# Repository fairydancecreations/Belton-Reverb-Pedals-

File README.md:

# Belton-Reverb-Pedals-
2 schims and pcb +gerbers for a BH2 and a BH3 belton brick reverbs. note the tone stack before the gain. seems stupid right ? have faith and try it with modulations. the BJT boost after is to give it level. both pcbs and circuits have parts to be included and changed to make overdrive versions. simply add the 2 soft clipping diodes . pick your fave and change the gain pot from 100k to 500k . this is a loud pedal so take the vol pot down to 50k if your speakers are in danger.

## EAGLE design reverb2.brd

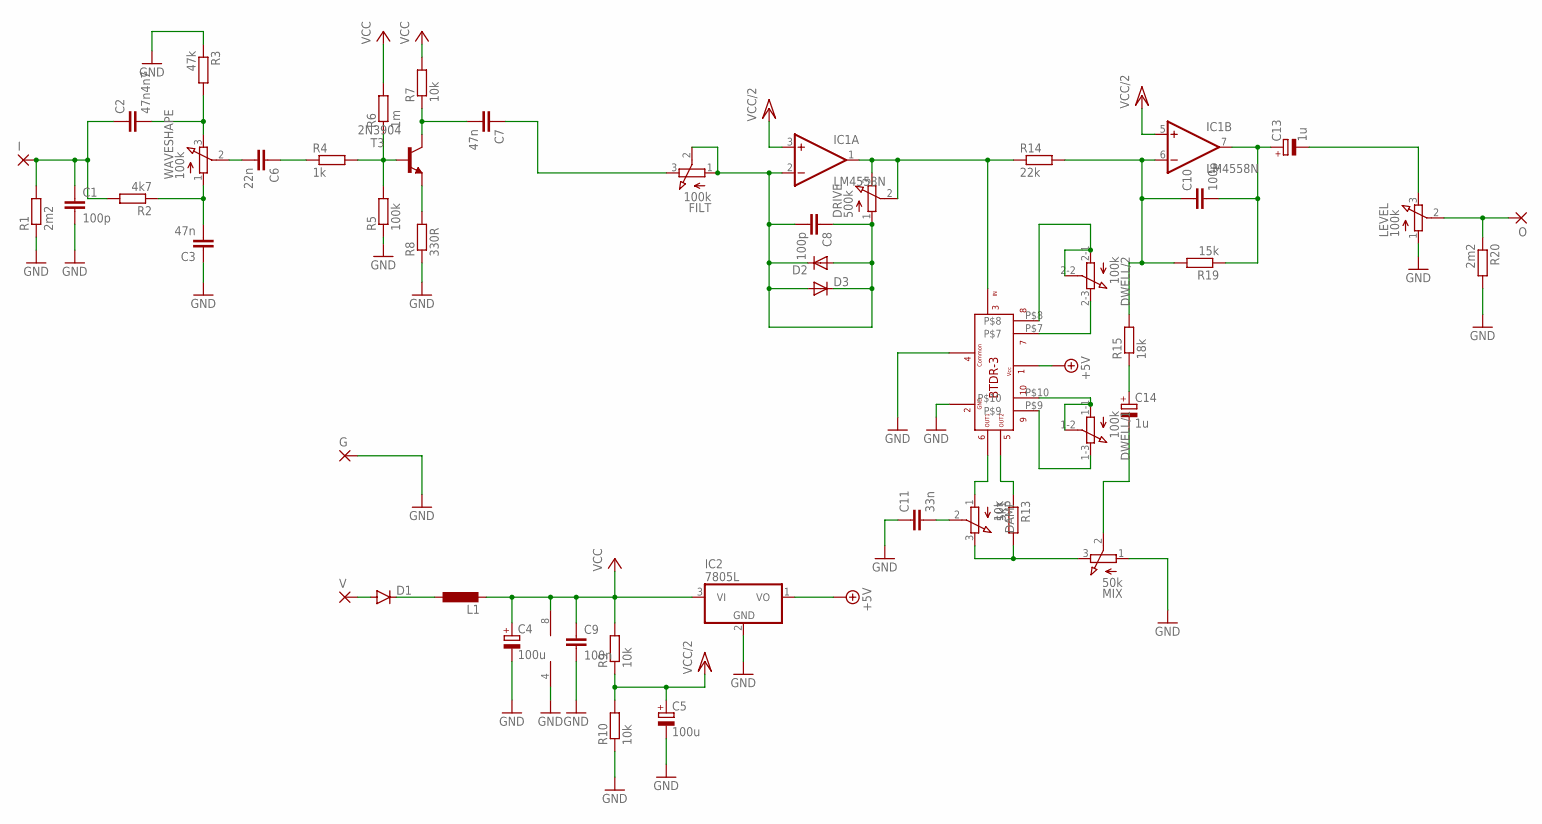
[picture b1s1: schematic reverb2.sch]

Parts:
C1, C8, C10: 100p; S5MMHEXCAP
C2: 47n4n7; S5MMHEXCAP
C3, C7: 47n; S5MMHEXCAP
C4, C5: 100u; E2,5-7
C6: 22n; S5MMHEXCAP
C9: 100n; S5MMHEXCAP
C11: 33n; S5MMHEXCAP
C13, C14: 1u; E2-4
D1: 1N4148DO35-7; DO35-7
D2, D3: SMALL_DIODEDO35-7; DO35-7
DAMP: 10k; 3RP/1610N
DRIVE: 500k; 3RP/1610N
DWELL: 100k; 3RP/1610G
FILT: 100k; 3RP/1610N
G: WIREPAD1,6/0,9; 1,6/0,9
I: WIREPAD1,6/0,9; 1,6/0,9
IC1: LM4558N; DIL08
IC2: 7805L; TO92
L1: L-EU0204/7; 0204/7
LEVEL: 100k; 3RP/1610N
MIX: 50k; 3RP/1610N
O: WIREPAD1,6/0,9; 1,6/0,9
R1, R20: 2m2; 0207/7
R2: 4k7; 0207/7
R3: 47k; 0207/7
R4: 1k; 0207/7
R5: 100k; 0207/7
R6: 1m; 0207/7
R7, R9, R10: 10k; 0207/7
R8: 330R; 0207/7
R13: 5k1; 0207/7
R14: 22k; 0207/7
R15: 18k; 0207/7
R19: 15k; 0207/7
T3: 2N3904; TO92
U$2: BTDR-3; BTDR3
V: WIREPAD1,6/0,9; 1,6/0,9
WAVESHAPE: 100k; 3RP/1610N

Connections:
+5V: IC2.1 (VO), U$2.P$1
GND: C1.2, C3.1, C4.-, C5.-, C9.2, C11.1, G.1, IC1.4 (V-), IC2.2 (GND), LEVEL.1 (A), MIX.1 (A), R1.1, R3.1, R5.1, R8.1, R10.1, R20.2, U$2.P$2, U$2.P$4
unnamed: R4.2, R5.2, R6.1, T3.2 (B)
unnamed: C7.2, R7.1, T3.1 (C)
unnamed: DWELL.2-3 (E), U$2.P$7
unnamed: R13.1, U$2.P$5
unnamed: DAMP.1 (A), U$2.P$6
unnamed: C7.1, FILT.3 (E)
unnamed: DAMP.3 (E), MIX.3 (E), R13.2
unnamed: D1.C, L1.1
unnamed: C2.2, R3.2, WAVESHAPE.3 (E)
unnamed: C13.-, LEVEL.3 (E)
unnamed: C14.-, MIX.2 (S)
unnamed: C11.2, DAMP.2 (S)
unnamed: C10.1, IC1.6 (-IN), R14.2, R15.2, R19.2
unnamed: C14.+, R15.1
unnamed: C6.1, R4.1
unnamed: C8.1, C8.2, D2.A, D2.C, D3.A, D3.C, DRIVE.1 (A), FILT.1 (A), FILT.2 (S), IC1.2 (-IN)
unnamed: C3.2, R2.1, WAVESHAPE.1 (A)
unnamed: R8.2, T3.3 (E)
unnamed: C1.1, C2.1, I.1, R1.2, R2.2
unnamed: C6.2, WAVESHAPE.2 (S)
unnamed: LEVEL.2 (S), O.1, R20.1
unnamed: D1.A, V.1
unnamed: DRIVE.2 (S), DRIVE.3 (E), IC1.1 (OUT), R14.1, U$2.P$3
unnamed: C10.2, C13.+, IC1.7 (OUT), R19.1
unnamed: DWELL.2-1 (A), DWELL.2-2 (S), U$2.P$8
unnamed: DWELL.1-3 (E), U$2.P$9
unnamed: DWELL.1-1 (A), DWELL.1-2 (S), U$2.P$10
VCC: C4.+, C9.1, IC1.8 (V+), IC2.3 (VI), L1.2, R6.2, R7.2, R9.2
VCC/2: C5.+, IC1.3 (+IN), IC1.5 (+IN), R9.1, R10.2

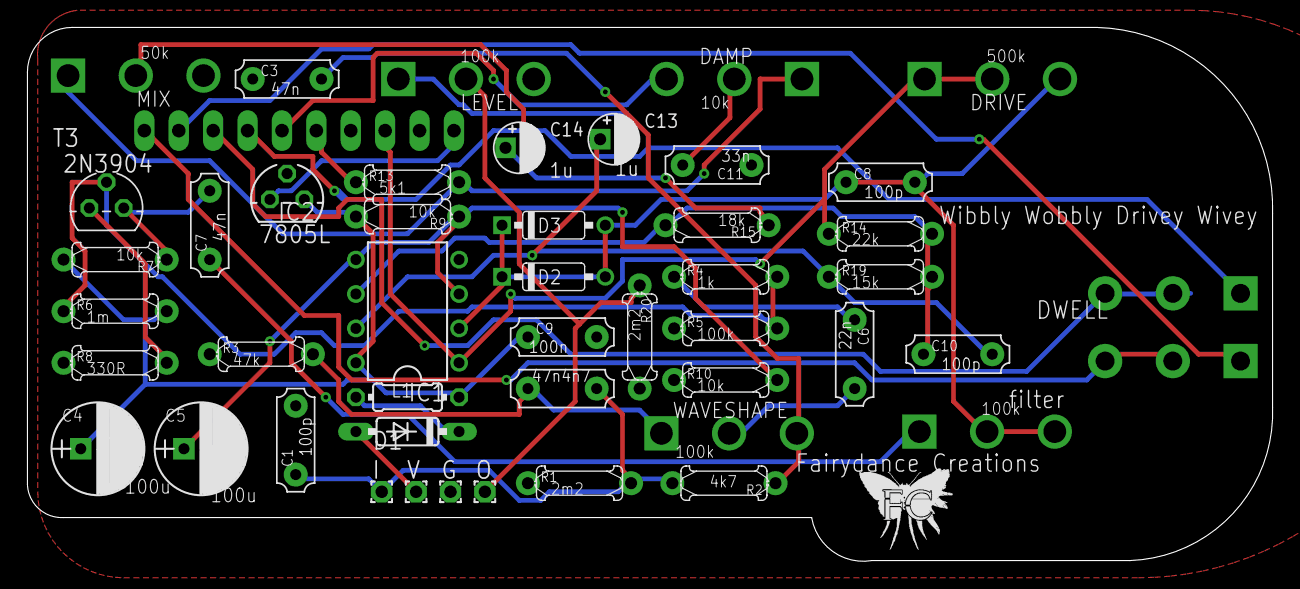
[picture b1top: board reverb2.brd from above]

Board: 2 copper layers, 91.9 x 39.4 mm, 47 parts (1 on the bottom side), 31 nets.
